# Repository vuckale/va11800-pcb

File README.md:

Required **[Daughterboard repository](https://github.com:vuckale/va11800-daughterboard)**

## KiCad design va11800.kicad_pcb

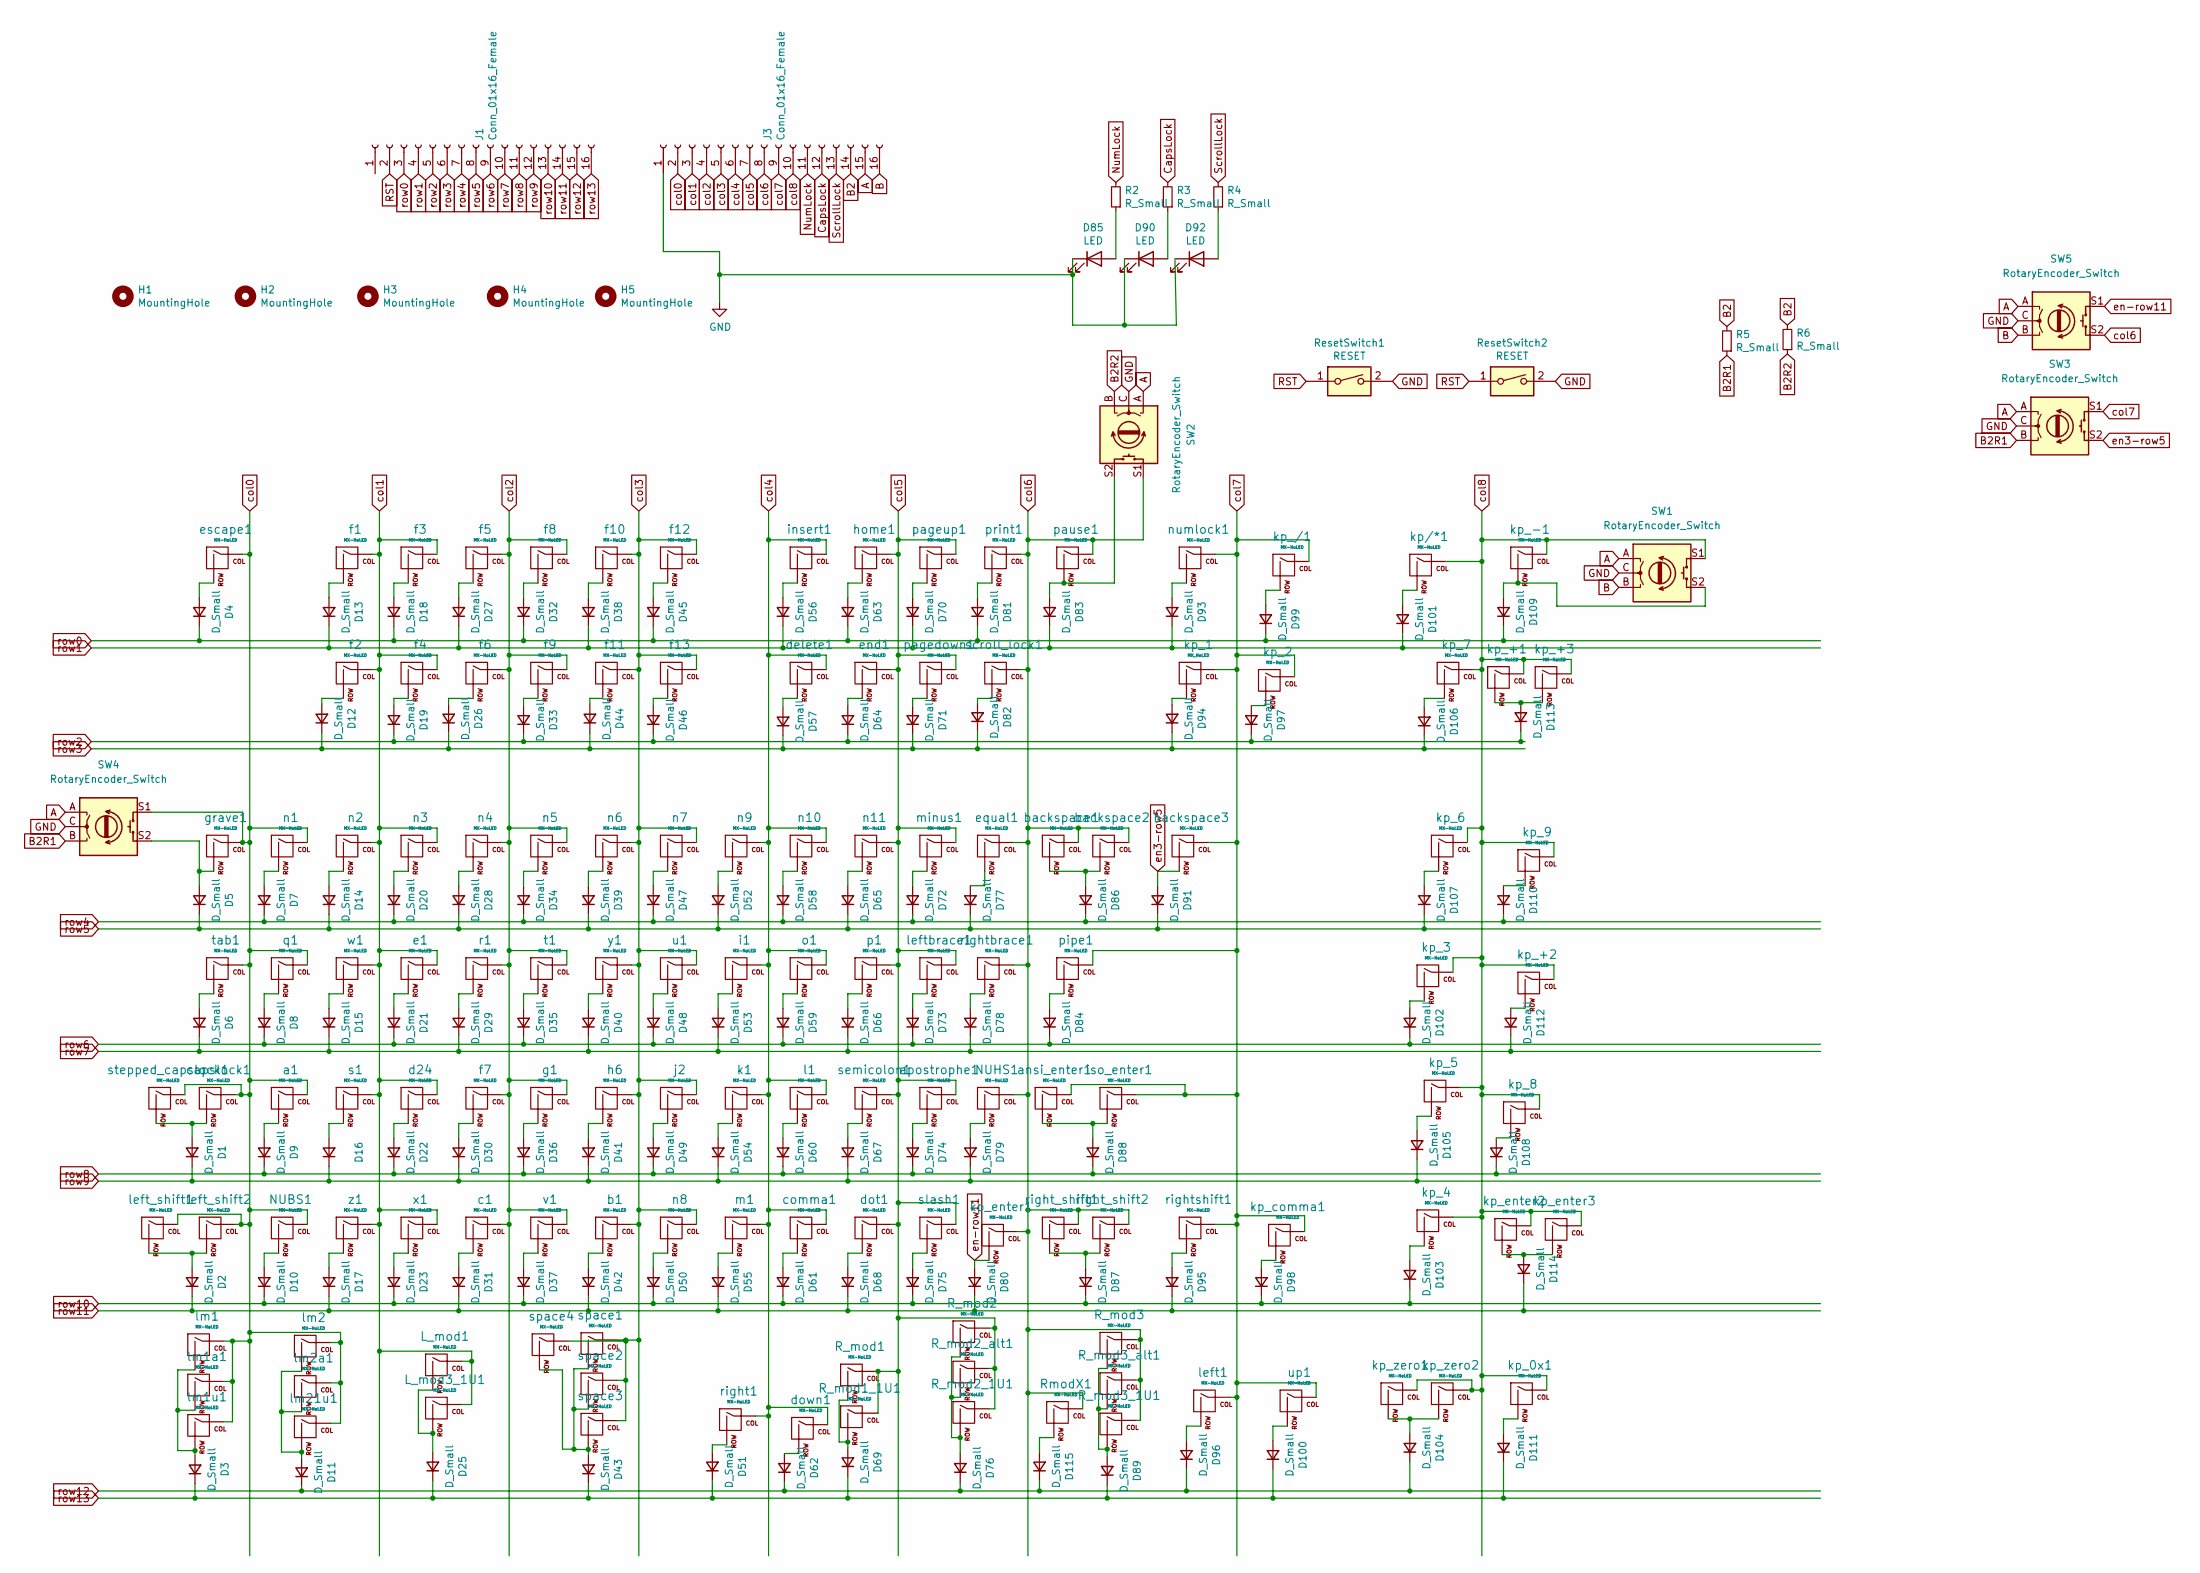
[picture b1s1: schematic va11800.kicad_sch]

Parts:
D1, D2, D3, D4, D5, D6, D7, D8, D9, D10, D11, D12, D13, D14, D15, D16, D17, D18, D19, D20, D21, D22, D23, D25, D26, D27, D28, D29, D30, D31, D32, D33, D34, D35, D36, D37, D38, D39, D40, D41, D42, D43, D44, D45, D46, D47, D48, D49, D50, D51, D52, D53, D54, D55, D56, D57, D58, D59, D60, D61, D62, D63, D64, D65, D66, D67, D68, D69, D70, D71, D72, D73, D74, D75, D76, D77, D78, D79, D80, D81, D82, D83, D84, D86, D87, D88, D89, D91, D93, D94, D95, D96, D97, D98, D99, D100, D101, D102, D103, D104, D105, D106, D107, D108, D109, D110, D111, D112, D113, D114, D115: D_Small; Diode-dual; LCSC C77978
D85, D90, D92: LED; LED_D2.00mm
H1, H2, H3, H4, H5: MountingHole; MountingHole_3.2mm_M3
J1, J3: Conn_01x16_Female; PinHeader_1x16_P2.54mm_Vertical
L_mod1: MX-NoLED; MXOnly-1.25U-NoLED
L_mod3_1U1: MX-NoLED; MXOnly-1U-NoLED
NUBS1: MX-NoLED; MXOnly-1U-NoLED
NUHS1: MX-NoLED; MXOnly-1U-NoLED
R2, R3, R4: R_Small; Resistor
R5, R6: R_Small; Resistor-Hybrid
R_mod1, R_mod2_alt1, R_mod3_alt1: MX-NoLED; MXOnly-1.25U-NoLED
R_mod1_1U1, R_mod2_1U1, R_mod3_1U1: MX-NoLED; MXOnly-1U-NoLED
R_mod2, R_mod3: MX-NoLED; MXOnly-1.5U-NoLED
ResetSwitch1, ResetSwitch2: RESET; SW_SPST_TL3342
RmodX1: MX-NoLED; MXOnly-1U-NoLED
SW1, SW2, SW3, SW4, SW5: RotaryEncoder_Switch; RotaryEncoder_EC11
a1: MX-NoLED; MXOnly-1U-NoLED
ansi_enter1: MX-NoLED; MXOnly-2.25U-NoLED
apostrophe1: MX-NoLED; MXOnly-1U-NoLED
b1: MX-NoLED; MXOnly-1U-NoLED
backspace1, backspace3: MX-NoLED; MXOnly-1U-NoLED
backspace2: MX-NoLED; MXOnly-2U-ReversedStabilizers-NoLED
c1: MX-NoLED; MXOnly-1U-NoLED
capslock1: MX-NoLED; MXOnly-1.75U-NoLED
comma1: MX-NoLED; MXOnly-1U-NoLED
d24: MX-NoLED; MXOnly-1U-NoLED
delete1: MX-NoLED; MXOnly-1U-NoLED
dot1: MX-NoLED; MXOnly-1U-NoLED
down1: MX-NoLED; MXOnly-1U-NoLED
e1: MX-NoLED; MXOnly-1U-NoLED
end1: MX-NoLED; MXOnly-1U-NoLED
equal1: MX-NoLED; MXOnly-1U-NoLED
escape1: MX-NoLED; MXOnly-1U-NoLED
f1, f2, f3: MX-NoLED; MXOnly-1U
f4, f5, f6, f7, f8, f9, f10, f11, f12, f13: MX-NoLED; MXOnly-1U-NoLED
g1: MX-NoLED; MXOnly-1U-NoLED
grave1: MX-NoLED; MXOnly-1U-NoLED
h6: MX-NoLED; MXOnly-1U-NoLED
home1: MX-NoLED; MXOnly-1U-NoLED
i1: MX-NoLED; MXOnly-1U-NoLED
insert1: MX-NoLED; MXOnly-1U-NoLED
iso_enter1: MX-NoLED; MXOnly-ISO-ReversedStabilizers-NoLED
j2: MX-NoLED; MXOnly-1U-NoLED
k1: MX-NoLED; MXOnly-1U-NoLED
kp/*1: MX-NoLED; MXOnly-1U-NoLED
kp_0x1, kp_2, kp_3, kp_4, kp_5, kp_6, kp_7, kp_8, kp_9: MX-NoLED; MXOnly-1U-NoLED
kp_1: MX_NoLED; MXOnly-1U-NoLED
kp_+1: MX-NoLED; MXOnly-2U-VerticalStabilizers-NoLED
kp_+2, kp_+3: MX-NoLED; MXOnly-1U-NoLED
kp_-1: MX-NoLED; MXOnly-1U-NoLED
kp_/1: MX-NoLED; MXOnly-1U-NoLED
kp_comma1: MX-NoLED; MXOnly-1U-NoLED
kp_enter1, kp_enter3: MX-NoLED; MXOnly-1U-NoLED
kp_enter2: MX-NoLED; MXOnly-2U-VerticalStabilizers-NoLED
kp_zero1: MX-NoLED; MXOnly-2U-ReversedStabilizers-NoLED
kp_zero2: MX-NoLED; MXOnly-1U-NoLED
l1: MX-NoLED; MXOnly-1U-NoLED
left1: MX-NoLED; MXOnly-1U-NoLED
left_shift1: MX-NoLED; MXOnly-1.25U-NoLED
left_shift2: MX-NoLED; MXOnly-2.25U-NoLED
leftbrace1: MX-NoLED; MXOnly-1U-NoLED
lm1, lm2: MX-NoLED; MXOnly-1.5U-NoLED
lm1a1, lm2a1: MX-NoLED; MXOnly-1.25U-NoLED
lm1u1, lm21u1: MX-NoLED; MXOnly-1U-NoLED
m1: MX-NoLED; MXOnly-1U-NoLED
minus1: MX-NoLED; MXOnly-1U-NoLED
n1, n2, n3, n4, n5, n6, n7, n8, n9, n10, n11: MX-NoLED; MXOnly-1U-NoLED
numlock1: MX-NoLED; MXOnly-1U-NoLED
o1: MX-NoLED; MXOnly-1U-NoLED
p1: MX-NoLED; MXOnly-1U-NoLED
pagedown1: MX-NoLED; MXOnly-1U-NoLED
pageup1: MX-NoLED; MXOnly-1U-NoLED
pause1: MX-NoLED; MXOnly-1U-NoLED
pipe1: MX-NoLED; MXOnly-1.5U-NoLED
print1: MX-NoLED; MXOnly-1U-NoLED
q1: MX-NoLED; MXOnly-1U-NoLED
r1: MX-NoLED; MXOnly-1U-NoLED
right1: MX-NoLED; MXOnly-1U-NoLED
right_shift1: MX-NoLED; MXOnly-1U-NoLED
right_shift2: MX-NoLED; MXOnly-2U-NoLED
rightbrace1: MX-NoLED; MXOnly-1U-NoLED
rightshift1: MX-NoLED; MXOnly-1U-NoLED
s1: MX-NoLED; MXOnly-1U-NoLED
scroll_lock1: MX-NoLED; MXOnly-1U-NoLED
semicolon1: MX-NoLED; MXOnly-1U-NoLED
slash1: MX-NoLED; MXOnly-1U-NoLED
space1: MX-NoLED; MXOnly-7U-NoLED
space2, space3: MX-NoLED; MXOnly-6.25U-NoLED
space4: MX-NoLED; MXOnly-6U-NoSwitch
stepped_capslock1: MX-NoLED; MXOnly-1.25U-NoLED
t1: MX-NoLED; MXOnly-1U-NoLED
tab1: MX-NoLED; MXOnly-1.5U-NoLED
u1: MX-NoLED; MXOnly-1U-NoLED
up1: MX-NoLED; MXOnly-1U-NoLED
v1: MX-NoLED; MXOnly-1U-NoLED
w1: MX-NoLED; MXOnly-1U-NoLED
x1: MX-NoLED; MXOnly-1U-NoLED
y1: MX-NoLED; MXOnly-1U-NoLED
z1: MX-NoLED; MXOnly-1U-NoLED

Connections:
A: J3.15, SW1.A, SW2.A, SW3.A, SW4.A, SW5.A
B: J3.16, SW1.B, SW5.B
B2: J3.14, R5.2, R6.2
B2R1: R5.1, SW3.B, SW4.B
B2R2: R6.1, SW2.B
CapsLock: J3.12, R3.2
GND: D85.1 (K), D90.1 (K), D92.1 (K), J3.1, ResetSwitch1.2, ResetSwitch2.2, SW1.C, SW2.C, SW3.C, SW4.C, SW5.C; also elsewhere on the board
unnamed: D1.2 (A), capslock1.2 (ROW), stepped_capslock1.2 (ROW)
unnamed: D2.2 (A), left_shift1.2 (ROW), left_shift2.2 (ROW)
unnamed: D3.2 (A), lm1.2 (ROW), lm1a1.2 (ROW), lm1u1.2 (ROW)
unnamed: D4.2 (A), escape1.2 (ROW)
unnamed: D5.2 (A), SW4.S2, grave1.2 (ROW)
unnamed: D6.2 (A), tab1.2 (ROW)
unnamed: D7.2 (A), n1.2 (ROW)
unnamed: D8.2 (A), q1.2 (ROW)
unnamed: D9.2 (A), a1.2 (ROW)
unnamed: D10.2 (A), NUBS1.2 (ROW)
unnamed: D11.2 (A), lm2.2 (ROW), lm2a1.2 (ROW), lm21u1.2 (ROW)
unnamed: D12.2 (A), f2.2 (ROW)
unnamed: D13.2 (A), f1.2 (ROW)
unnamed: D14.2 (A), n2.2 (ROW)
unnamed: D15.2 (A), w1.2 (ROW)
unnamed: D16.2 (A), s1.2 (ROW)
unnamed: D17.2 (A), z1.2 (ROW)
unnamed: D18.2 (A), f3.2 (ROW)
unnamed: D19.2 (A), f4.2 (ROW)
unnamed: D20.2 (A), n3.2 (ROW)
unnamed: D21.2 (A), e1.2 (ROW)
unnamed: D22.2 (A), d24.2 (ROW)
unnamed: D23.2 (A), x1.2 (ROW)
unnamed: D25.2 (A), L_mod1.2 (ROW), L_mod3_1U1.2 (ROW)
unnamed: D26.2 (A), f6.2 (ROW)
unnamed: D27.2 (A), f5.2 (ROW)
unnamed: D28.2 (A), n4.2 (ROW)
unnamed: D29.2 (A), r1.2 (ROW)
unnamed: D30.2 (A), f7.2 (ROW)
unnamed: D31.2 (A), c1.2 (ROW)
unnamed: D32.2 (A), f8.2 (ROW)
unnamed: D33.2 (A), f9.2 (ROW)
unnamed: D34.2 (A), n5.2 (ROW)
unnamed: D35.2 (A), t1.2 (ROW)
unnamed: D36.2 (A), g1.2 (ROW)
unnamed: D37.2 (A), v1.2 (ROW)
unnamed: D38.2 (A), f10.2 (ROW)
unnamed: D39.2 (A), n6.2 (ROW)
unnamed: D40.2 (A), y1.2 (ROW)
unnamed: D41.2 (A), h6.2 (ROW)
unnamed: D42.2 (A), b1.2 (ROW)
unnamed: D43.2 (A), space1.2 (ROW), space2.2 (ROW), space3.2 (ROW)
unnamed: D44.2 (A), f11.2 (ROW)
unnamed: D45.2 (A), f12.2 (ROW)
unnamed: D46.2 (A), f13.2 (ROW)
unnamed: D47.2 (A), n7.2 (ROW)
unnamed: D48.2 (A), u1.2 (ROW)
unnamed: D49.2 (A), j2.2 (ROW)
unnamed: D50.2 (A), n8.2 (ROW)
unnamed: D51.2 (A), right1.2 (ROW)
unnamed: D52.2 (A), n9.2 (ROW)
unnamed: D53.2 (A), i1.2 (ROW)
unnamed: D54.2 (A), k1.2 (ROW)
unnamed: D55.2 (A), m1.2 (ROW)
unnamed: D56.2 (A), insert1.2 (ROW)
unnamed: D57.2 (A), delete1.2 (ROW)
unnamed: D58.2 (A), n10.2 (ROW)
unnamed: D59.2 (A), o1.2 (ROW)
unnamed: D60.2 (A), l1.2 (ROW)
unnamed: D61.2 (A), comma1.2 (ROW)
unnamed: D62.2 (A), down1.2 (ROW)
unnamed: D63.2 (A), home1.2 (ROW)
unnamed: D64.2 (A), end1.2 (ROW)
unnamed: D65.2 (A), n11.2 (ROW)
unnamed: D66.2 (A), p1.2 (ROW)
unnamed: D67.2 (A), semicolon1.2 (ROW)
unnamed: D68.2 (A), dot1.2 (ROW)
unnamed: D69.2 (A), R_mod1.2 (ROW), R_mod1_1U1.2 (ROW)
unnamed: D70.2 (A), pageup1.2 (ROW)
unnamed: D71.2 (A), pagedown1.2 (ROW)
unnamed: D72.2 (A), minus1.2 (ROW)
unnamed: D73.2 (A), leftbrace1.2 (ROW)
unnamed: D74.2 (A), apostrophe1.2 (ROW)
unnamed: D75.2 (A), slash1.2 (ROW)
unnamed: D76.2 (A), R_mod2.2 (ROW), R_mod2_1U1.2 (ROW), R_mod2_alt1.2 (ROW)
unnamed: D77.2 (A), equal1.2 (ROW)
unnamed: D78.2 (A), rightbrace1.2 (ROW)
unnamed: D79.2 (A), NUHS1.2 (ROW)
unnamed: D81.2 (A), print1.2 (ROW)
unnamed: D82.2 (A), scroll_lock1.2 (ROW)
unnamed: D83.2 (A), SW2.S2, pause1.2 (ROW)
unnamed: D84.2 (A), pipe1.2 (ROW)
unnamed: D85.2 (A), R2.1
unnamed: D86.2 (A), backspace1.2 (ROW), backspace2.2 (ROW)
unnamed: D87.2 (A), right_shift1.2 (ROW), right_shift2.2 (ROW)
unnamed: D88.2 (A), ansi_enter1.2 (ROW), iso_enter1.2 (ROW)
unnamed: D89.2 (A), R_mod3.2 (ROW), R_mod3_1U1.2 (ROW), R_mod3_alt1.2 (ROW)
unnamed: D90.2 (A), R3.1
unnamed: D92.2 (A), R4.1
unnamed: D93.2 (A), numlock1.2 (ROW)
unnamed: D94.2 (A), kp_1.2 (ROW)
unnamed: D95.2 (A), rightshift1.2 (ROW)
unnamed: D96.2 (A), left1.2 (ROW)
unnamed: D97.2 (A), kp_2.2 (ROW)
unnamed: D98.2 (A), kp_comma1.2 (ROW)
unnamed: D99.2 (A), kp_/1.2 (ROW)
unnamed: D100.2 (A), up1.2 (ROW)
unnamed: D101.2 (A), kp/*1.2 (ROW)
unnamed: D102.2 (A), kp_3.2 (ROW)
unnamed: D103.2 (A), kp_4.2 (ROW)
unnamed: D104.2 (A), kp_zero1.2 (ROW), kp_zero2.2 (ROW)
unnamed: D105.2 (A), kp_5.2 (ROW)
unnamed: D106.2 (A), kp_7.2 (ROW)
unnamed: D107.2 (A), kp_6.2 (ROW)
unnamed: D108.2 (A), kp_8.2 (ROW)
unnamed: D109.2 (A), SW1.S2, kp_-1.2 (ROW)
unnamed: D110.2 (A), kp_9.2 (ROW)
unnamed: D111.2 (A), kp_0x1.2 (ROW)
unnamed: D112.2 (A), kp_+2.2 (ROW)
unnamed: D113.2 (A), kp_+1.2 (ROW), kp_+3.2 (ROW)
unnamed: D114.2 (A), kp_enter2.2 (ROW), kp_enter3.2 (ROW)
unnamed: D115.2 (A), RmodX1.2 (ROW)
NumLock: J3.11, R2.2
RST: J1.2, ResetSwitch1.1, ResetSwitch2.1
ScrollLock: J3.13, R4.2
col0: J3.2, NUBS1.1 (COL), SW4.S1, a1.1 (COL), capslock1.1 (COL), escape1.1 (COL), grave1.1 (COL), left_shift1.1 (COL), left_shift2.1 (COL), lm1.1 (COL), lm1a1.1 (COL), lm1u1.1 (COL), lm2.1 (COL), lm2a1.1 (COL), lm21u1.1 (COL), n1.1 (COL), q1.1 (COL), stepped_capslock1.1 (COL), tab1.1 (COL)
col1: J3.3, L_mod1.1 (COL), L_mod3_1U1.1 (COL), d24.1 (COL), e1.1 (COL), f1.1 (COL), f2.1 (COL), f3.1 (COL), f4.1 (COL), n2.1 (COL), n3.1 (COL), s1.1 (COL), w1.1 (COL), x1.1 (COL), z1.1 (COL)
col2: J3.4, c1.1 (COL), f5.1 (COL), f6.1 (COL), f7.1 (COL), f8.1 (COL), f9.1 (COL), g1.1 (COL), n4.1 (COL), n5.1 (COL), r1.1 (COL), t1.1 (COL), v1.1 (COL)
col3: J3.5, b1.1 (COL), f10.1 (COL), f11.1 (COL), f12.1 (COL), f13.1 (COL), h6.1 (COL), j2.1 (COL), n6.1 (COL), n7.1 (COL), n8.1 (COL), space1.1 (COL), space2.1 (COL), space3.1 (COL), u1.1 (COL), y1.1 (COL)
col4: J3.6, comma1.1 (COL), delete1.1 (COL), down1.1 (COL), i1.1 (COL), insert1.1 (COL), k1.1 (COL), l1.1 (COL), m1.1 (COL), n9.1 (COL), n10.1 (COL), o1.1 (COL), right1.1 (COL)
col5: J3.7, R_mod1.1 (COL), R_mod1_1U1.1 (COL), R_mod2.1 (COL), R_mod2_1U1.1 (COL), R_mod2_alt1.1 (COL), apostrophe1.1 (COL), dot1.1 (COL), end1.1 (COL), home1.1 (COL), leftbrace1.1 (COL), minus1.1 (COL), n11.1 (COL), p1.1 (COL), pagedown1.1 (COL), pageup1.1 (COL), semicolon1.1 (COL), slash1.1 (COL)
col6: J3.8, NUHS1.1 (COL), R_mod3.1 (COL), R_mod3_1U1.1 (COL), R_mod3_alt1.1 (COL), RmodX1.1 (COL), SW2.S1, SW5.S2, backspace1.1 (COL), backspace2.1 (COL), equal1.1 (COL), kp_enter1.1 (COL), pause1.1 (COL), print1.1 (COL), right_shift1.1 (COL), right_shift2.1 (COL), rightbrace1.1 (COL), scroll_lock1.1 (COL)
col7: J3.9, SW3.S1, ansi_enter1.1 (COL), backspace3.1 (COL), iso_enter1.1 (COL), kp_1.1 (COL), kp_2.1 (COL), kp_/1.1 (COL), kp_comma1.1 (COL), left1.1 (COL), numlock1.1 (COL), pipe1.1 (COL), rightshift1.1 (COL), up1.1 (COL)
col8: J3.10, SW1.S1, kp/*1.1 (COL), kp_0x1.1 (COL), kp_3.1 (COL), kp_4.1 (COL), kp_5.1 (COL), kp_6.1 (COL), kp_7.1 (COL), kp_8.1 (COL), kp_9.1 (COL), kp_+1.1 (COL), kp_+2.1 (COL), kp_+3.1 (COL), kp_-1.1 (COL), kp_enter2.1 (COL), kp_enter3.1 (COL), kp_zero1.1 (COL), kp_zero2.1 (COL)
en3-row5: D91.2 (A), SW3.S2, backspace3.2 (ROW)
en-row11: D80.2 (A), SW5.S1, kp_enter1.2 (ROW)
row0: D4.1 (K), D18.1 (K), D32.1 (K), D45.1 (K), D63.1 (K), D81.1 (K), D99.1 (K), D109.1 (K), J1.3
row1: D13.1 (K), D27.1 (K), D38.1 (K), D56.1 (K), D70.1 (K), D83.1 (K), D93.1 (K), D101.1 (K), J1.4
row2: D19.1 (K), D33.1 (K), D46.1 (K), D64.1 (K), D97.1 (K), D113.1 (K), J1.5
row3: D12.1 (K), D26.1 (K), D44.1 (K), D57.1 (K), D71.1 (K), D82.1 (K), D94.1 (K), D106.1 (K), J1.6
row4: D7.1 (K), D20.1 (K), D34.1 (K), D47.1 (K), D58.1 (K), D72.1 (K), D86.1 (K), D110.1 (K), J1.7
row5: D5.1 (K), D14.1 (K), D28.1 (K), D39.1 (K), D52.1 (K), D65.1 (K), D77.1 (K), D91.1 (K), D107.1 (K), J1.8
row6: D8.1 (K), D21.1 (K), D35.1 (K), D48.1 (K), D59.1 (K), D73.1 (K), D84.1 (K), D102.1 (K), J1.9
row7: D6.1 (K), D15.1 (K), D29.1 (K), D40.1 (K), D53.1 (K), D66.1 (K), D78.1 (K), D112.1 (K), J1.10
row8: D9.1 (K), D22.1 (K), D36.1 (K), D49.1 (K), D60.1 (K), D74.1 (K), D88.1 (K), D108.1 (K), J1.11
row9: D1.1 (K), D16.1 (K), D30.1 (K), D41.1 (K), D54.1 (K), D67.1 (K), D79.1 (K), D105.1 (K), J1.12
row10: D10.1 (K), D23.1 (K), D37.1 (K), D50.1 (K), D61.1 (K), D75.1 (K), D87.1 (K), D98.1 (K), D103.1 (K), J1.13
row11: D2.1 (K), D17.1 (K), D31.1 (K), D42.1 (K), D55.1 (K), D68.1 (K), D80.1 (K), D95.1 (K), D114.1 (K), J1.14
row12: D11.1 (K), D62.1 (K), D76.1 (K), D96.1 (K), D104.1 (K), D115.1 (K), J1.15
row13: D3.1 (K), D25.1 (K), D43.1 (K), D51.1 (K), D69.1 (K), D89.1 (K), D100.1 (K), D111.1 (K), J1.16

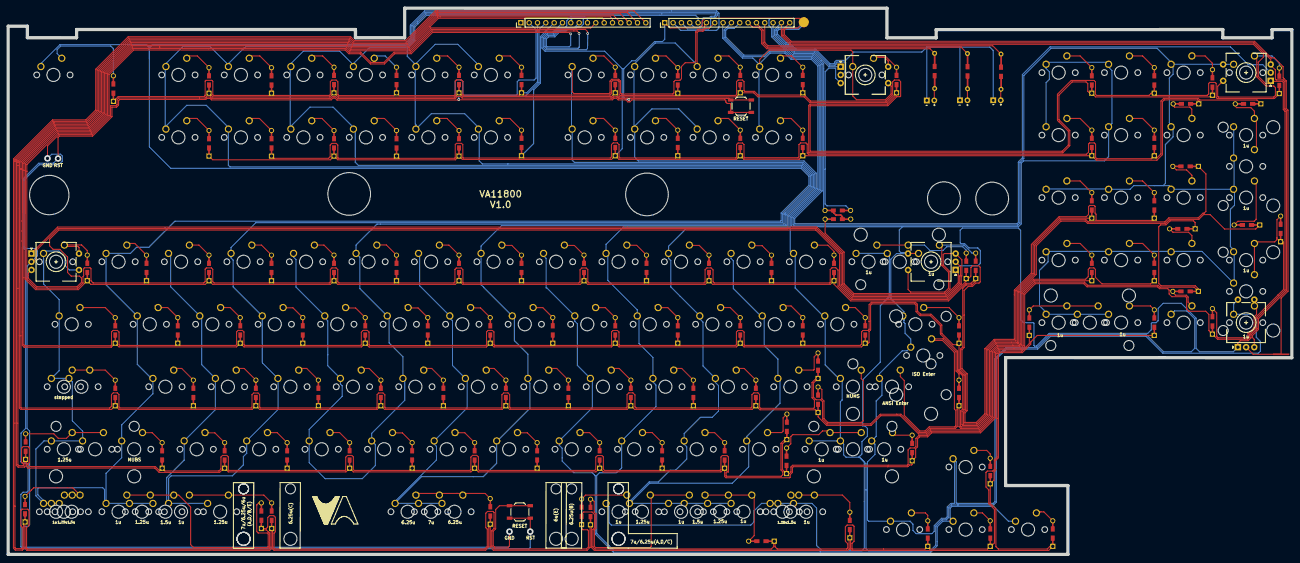
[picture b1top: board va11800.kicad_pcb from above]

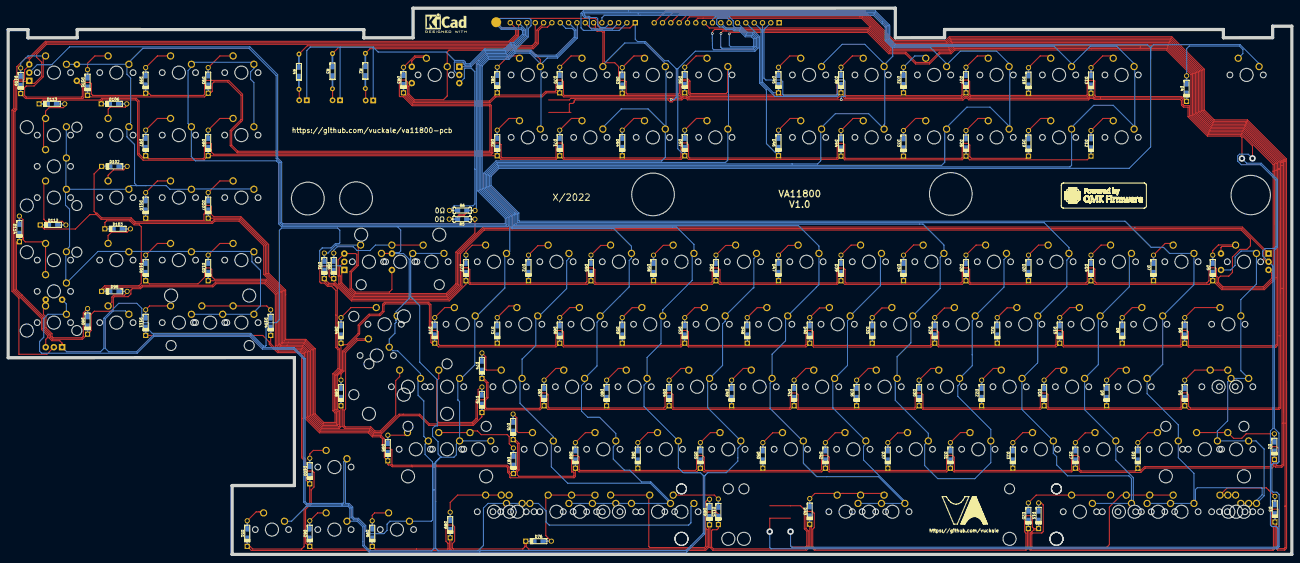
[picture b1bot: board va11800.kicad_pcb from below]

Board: 2 copper layers, 391.2 x 166.5 mm, 268 parts (122 on the bottom side), 147 nets.

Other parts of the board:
J6, J6#2: D2; SinglePad
Kicad: KiCad-Logo2_5mm_SilkScreen

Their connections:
GND: J6.1, J6#2.1; also elsewhere on the board
